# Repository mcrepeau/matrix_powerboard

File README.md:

# MatrixChain Power Board

Custom power board that feeds **four 32×32 HUB75 LED panels (4096 LEDs)** plus the **Adafruit
MatrixPortal S3** from one USB-C PD source (requested contract **20V/3A = 60W**, standard 3A cable).

Board **Rev A**: 58.35 × 50.5 mm, 2-layer 1.6 mm (1 oz default, order 2 oz if offered), all SMD on
top except the J3–J5 THT screw terminals. Orderable BOM with MPN + LCSC codes: `hardware/powerboard.csv`.

The MatrixPortal S3's MCU can drive up to 4096 LEDs, but its own USB-C port only supplies 5V/3A —
about 1500 LEDs at full white. This board lets the Portal run at full capacity: the Portal drives the
HUB75 data lines, the board supplies the panel power externally.

- **[DATASHEET.md](hardware/DATASHEET.md)** — the board's user-facing spec: electrical characteristics, connector
  pinouts, LED meanings, firmware interface, key components, assembly/bring-up.
- **[DESIGN.md](hardware/DESIGN.md)** — full design rationale, net list, per-pin hookup tables, component-selection rationale, layout and
  safety notes, open items. Source of truth for the schematic.

## Connections

```
USB-C adapter ──► PowerBoard USB-C connector (J1) ──► D1 red LED on /POW_EN (input invalid); D2/D3 green per channel
					└─ I2C connector (J2) ─► Adafruit MatrixPortal I2C connector
					└─ Screw terminals (J3) ─► Adafruit MatrixPortal power terminals (≤1A)
					└─ Screw terminals (J4) ─► HUB75 panels 1-2 (<5A)
					└─ Screw terminals (J5) ─► HUB75 panels 3-4 (<5A)
          
```

Portal links: **J3** (5V tap, ≤1A, to the M3 power screw terminals) and **J2** STEMMA QT
(GND, +3.3V, SDA, SCL). The HUB75 link to the Portal carries **data + GND only, no power** — do not
connect its 5V pins. There is no CH_EN/PG line: channels are gated purely by the supervisor
(input ≥ ≈8V ⇒ `/POW_EN` high). Panel power plugs are not reverse-protected — observe polarity.

## Behavior

| Condition | Input | D1 (red) | D2/D3 (green) | Channels | Firmware |
|---|---|---|---|---|---|
| Good PD source | ≈20V | off | on | on | read HUSB238 contract, cap power at 85% of V×I, run governor on INA226s |
| Lower contract (e.g. 15V/3A) | ≈15V | off | on | on | cap to 85% of V×I, log contract |
| Overcurrent | ≈20V | off | off (faulted ch) | limit/hiccup | INA226 alert (register) + governor |
| Dumb 5V source | ≈5V | **on** | off | off | Portal may still boot; report missing contract |
| Unplugged | 0V | off | off | off | — |

## Firmware interface

I2C on the QT bus (3.3V): HUSB238 **0x08** (source caps / negotiated contract / PDO select),
INA226 **0x40** (ch1) and **0x44** (ch2) — program CAL (0x05) at boot, alert ≈4.8A via Mask/Enable 0x06.
Boot: blank HUB75 ASAP (channels auto-enable at input ≥ ≈8V) → read contract → set power cap →
program INA226 → run (read sensors every 100ms; brightness down if a channel >4.6A for 3 reads).
Details and register maps: DATASHEET.md; rationale: DESIGN.md §5.

## Safety

Panels are **5V only**. 20V@3A and 5V@8.4A are high-energy: protection is the U9 TVS2200DRV clamp on
VBUS + HUSB238 OVP (24V) + Q1 disconnect, per-rail PTC fuses (F1 1206L100/12NR tap, F2/F3
2920L700/12MR channels), converter current limits — never rely on software for hard limits.
No input fuse (compliant PD sources only / current-limited bench supply).
Strain-relieve all cables. Full notes: DESIGN.md §9.

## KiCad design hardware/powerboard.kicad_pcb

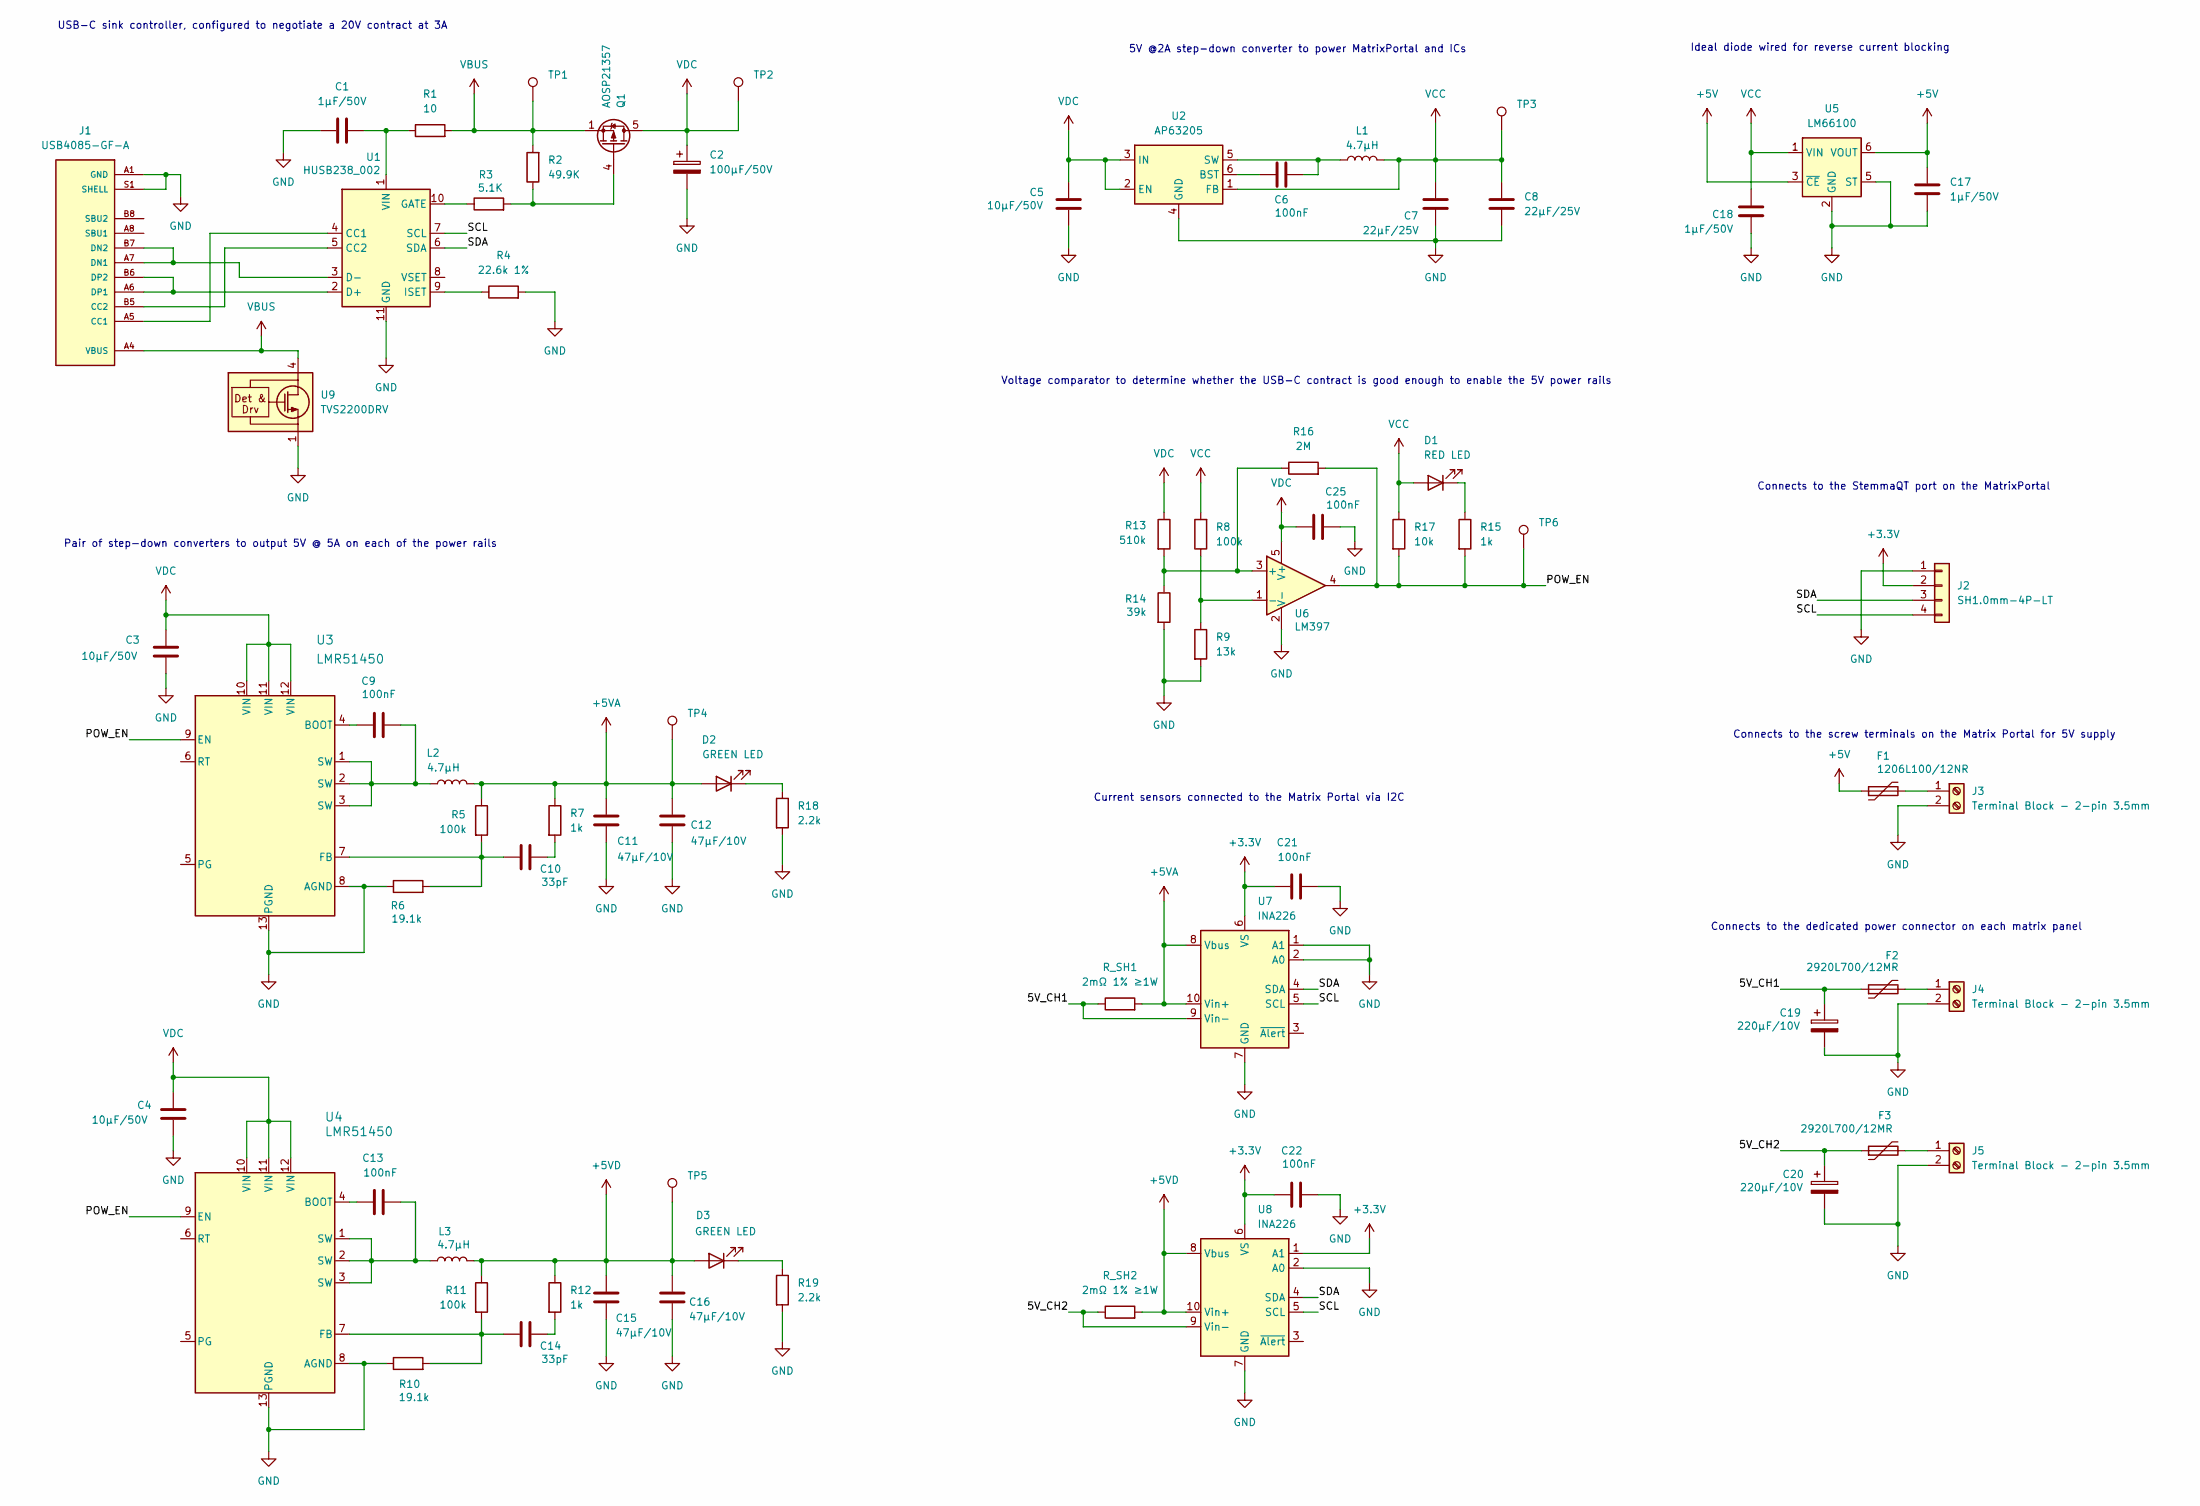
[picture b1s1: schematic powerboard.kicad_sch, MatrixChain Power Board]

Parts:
C1, C17, C18: 1µF/50V; C_0603_1608Metric; Part Number CL10A105KB8NNNC; LCSC Part # C15849
C2: 100µF/50V; CP_Elec_10x10.5; Part Number 50PEV100M10X10.5; LCSC Part # C2161609
C3, C4, C5: 10µF/50V; C_0805_2012Metric; Part Number GRM21BR61H106KE43L; LCSC Part # C440198
C6, C9, C13, C21, C22, C25: 100nF; C_0603_1608Metric; Part Number CC0603KRX7R9BB104; LCSC Part # C14663
C7, C8: 22µF/25V; C_0805_2012Metric; Part Number CL21A226MAQNNNE; LCSC Part # C45783
C10, C14: 33pF; C_0603_1608Metric; Part Number CL10C330JB8NNNC; LCSC Part # C1663
C11, C12, C15, C16: 47µF/10V; C_1206_3216Metric; Part Number CL31A476MPHNNNE; LCSC Part # C96123
C19, C20: 220µF/10V; CP_Elec_6.3x7.7; Part Number EEEFPA221XAP; LCSC Part # C278407
D1: RED LED; LED_0805_2012Metric; Part Number NCD0805R1; LCSC Part # C84256
D2, D3: GREEN LED; LED_0805_2012Metric; Part Number KT-0805G; LCSC Part # C2297
F1: 1206L100/12NR; Fuse_1206_3216Metric; Part Number 1206L100/12NR; LCSC Part # C55089856
F2, F3: 2920L700/12MR; Fuse_2920_7451Metric; Part Number 2920L700/12MR; LCSC Part # C207092
J1: USB4085-GF-A; GCT_USB4085-GF-A_REVA4; MPN USB4085-GF-A; LCSC Part # C7095263
J2: SH1.0mm-4P-LT; JST_SH_BM04B-SRSS-TB_1x04-1MP_P1.00mm_Vertical; Part Number BM04B-SRSS-TB; LCSC Part # C160390
J3, J4, J5: Terminal Block - 2-pin 3.5mm; TerminalBlock_Phoenix_PT-1,5-2-3.5-H_1x02_P3.50mm_Horizontal
L1, L2, L3: 4.7µH; L_Coilank_AAPS0650_7.7x6.6mm; Part Number APS0650M4R7A; LCSC Part # C47327217
Q1: AOSP21357; SO8SOP-8L_AOS-L; Part Number AOSP21357; LCSC Part # C541725
R1: 10; R_0603_1608Metric; Part Number 0603WAF100JT5E; LCSC Part # C22859
R2: 49.9K; R_0603_1608Metric; Part Number 0603WAF4992T5E; LCSC Part # C23184
R3: 5.1K; R_0603_1608Metric; Part Number 0603WAF5101T5E; LCSC Part # C23186
R4: 22.6k 1%; R_0603_1608Metric; Part Number CR0603FA2262G; LCSC Part # C100874
R5, R8, R11: 100k; R_0603_1608Metric; Part Number 0603WAF1003T5E; LCSC Part # C25803
R6, R10: 19.1k; R_0603_1608Metric; Part Number CR0603FA1912G; LCSC Part # C100835
R7, R12, R15: 1k; R_0603_1608Metric; Part Number 0603WAF1001T5E; LCSC Part # C21190
R9: 13k; R_0603_1608Metric; Part Number 0603WAF1302T5E; LCSC Part # C22797
R13: 510k; R_0603_1608Metric; Part Number 0603WAF5103T5E; LCSC Part # C23192
R14: 39k; R_0603_1608Metric; Part Number 0603WAF3902T5E; LCSC Part # C23153
R16: 2M; R_0603_1608Metric; Part Number 0603WAF2004T5E; LCSC Part # C22976
R17: 10k; R_0603_1608Metric; Part Number 0603WAF1002T5E; LCSC Part # C25804
R18, R19: 2.2k; R_0603_1608Metric; Part Number 0603WAF2201T5E; LCSC Part # C4190
R_SH1, R_SH2: 2mΩ 1% ≥1W; R_2512_6332Metric; Part Number RLP25FEER002; LCSC Part # C160590
TP1, TP2, TP3, TP4, TP5, TP6: TestPoint; TestPoint_Pad_D2.0mm
U1: HUSB238_002; WDFN-10-1EP_3x3mm_P0.5mm_EP1.8x2.5mm; Part Number HUSB238_002DD; LCSC Part # C7471904
U2: AP63205; TSOT-23-6; Part Number AP63205WU-7; LCSC Part # C2071056
U3, U4: LMR51450; WSON_SDRRR_TEX; Part Number LMR51450SDRRR; LCSC Part # C6890985
U5: LM66100; SOT-363_SC-70-6; Part Number LM66100DCK; LCSC Part # C2832141
U6: LM397; SOT-23-5; Part Number LM397MFX/NOPB; LCSC Part # C132076
U7, U8: INA226; TSSOP-10_3x3mm_P0.5mm; Part Number INA226AIDGSR; LCSC Part # C49851
U9: TVS2200DRV; WSON-6-1EP_2x2mm_P0.65mm_EP1x1.6mm; Part Number LMTVS2200DRVR; LCSC Part # C49330883

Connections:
+3.3V: C21.1, C22.1, J2.2, U7.6 (VS), U8.1 (A1), U8.6 (VS)
+5V: C17.1, F1.1, U5.3 (~CE), U5.6 (VOUT)
+5VA: C11.1, C12.1, D2.2 (A), L2.2, R5.1, R7.1, R_SH1.2, TP4.1 (1_1), U7.8 (Vbus), U7.10 (Vin+)
+5VD: C15.1, C16.1, D3.2 (A), L3.2, R11.1, R12.1, R_SH2.2, TP5.1 (1_1), U8.8 (Vbus), U8.10 (Vin+)
/5V_CH1: C19.1, F2.1, R_SH1.1, U7.9 (Vin-)
/5V_CH2: C20.1, F3.1, R_SH2.1, U8.9 (Vin-)
/POW_EN: R15.2, R16.2, R17.2, TP6.1 (1_1), U3.9 (EN), U4.9 (EN), U6.4
/SCL: J2.4, U1.7 (SCL), U7.5 (SCL), U8.5 (SCL)
/SDA: J2.3, U1.6 (SDA), U7.4 (SDA), U8.4 (SDA)
GND: C1.1, C2.2, C3.2, C4.2, C5.2, C7.2, C8.2, C11.2, C12.2, C15.2, C16.2, C17.2, C18.2, C19.2, C20.2, C21.2, C22.2, C25.2, J1.A1 (GND), J1.A12 (GND), J1.B1 (GND), J1.B12 (GND), J1.S1 (SHELL), J1.S2 (SHELL), J1.S3 (SHELL), J1.S4 (SHELL), J2.1, J3.2, J4.2, J5.2, R4.2, R6.1, R9.2, R10.1, R14.2, R18.2, R19.2, U1.11 (GND), U2.4 (GND), U3.8 (AGND), U3.13 (PGND), U4.8 (AGND), U4.13 (PGND), U5.2 (GND), U5.5 (ST), U6.2 (V-), U7.1 (A1), U7.2 (A0), U7.7 (GND), U8.2 (A0), U8.7 (GND), U9.1 (GND), U9.2 (GND), U9.3 (GND), U9.7 (GND)
unnamed: C9.2, L2.1, U3.1 (SW), U3.2 (SW), U3.3 (SW)
unnamed: C10.2, R7.2
unnamed: C13.2, L3.1, U4.1 (SW), U4.2 (SW), U4.3 (SW)
unnamed: C14.2, R12.2
unnamed: D1.1 (K), R15.1
unnamed: D2.1 (K), R18.1
unnamed: D3.1 (K), R19.1
unnamed: J1.A5 (CC1), U1.4 (CC1)
unnamed: J1.B5 (CC2), U1.5 (CC2)
unnamed: J1.A7 (DN1), J1.B7 (DN2), U1.3 (D-)
unnamed: J1.A6 (DP1), J1.B6 (DP2), U1.2 (D+)
unnamed: F1.2, J3.1
unnamed: F2.2, J4.1
unnamed: F3.2, J5.1
unnamed: Q1.4 (G), R2.1, R3.2
unnamed: R3.1, U1.10 (GATE)
unnamed: R4.1, U1.9 (ISET)
unnamed: C1.2, R1.1, U1.1 (VIN)
unnamed: C6.1, U2.6 (BST)
unnamed: C6.2, L1.1, U2.5 (SW)
unnamed: C9.1, U3.4 (BOOT)
unnamed: C10.1, R5.2, R6.2, U3.7 (FB)
unnamed: C13.1, U4.4 (BOOT)
unnamed: C14.1, R10.2, R11.2, U4.7 (FB)
unnamed: R13.2, R14.1, R16.1, U6.3 (+)
unnamed: R8.1, R9.1, U6.1 (-)
VBUS: J1.A4 (VBUS), J1.A9 (VBUS), J1.B4 (VBUS), J1.B9 (VBUS), Q1.1 (S), Q1.2 (S), Q1.3 (S), R1.2, R2.2, TP1.1 (1_1), U9.4 (IN), U9.5 (IN), U9.6 (IN)
VCC: C7.1, C8.1, C18.1, D1.2 (A), L1.2, R8.2, R17.1, TP3.1 (1_1), U2.1 (FB), U5.1 (VIN)
VDC: C2.1, C3.1, C4.1, C5.1, C25.1, Q1.5 (D), Q1.6 (D), Q1.7 (D), Q1.8 (D), R13.1, TP2.1 (1_1), U2.2 (EN), U2.3 (IN), U3.10 (VIN), U3.11 (VIN), U3.12 (VIN), U4.10 (VIN), U4.11 (VIN), U4.12 (VIN), U6.5 (V+)

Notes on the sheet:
Connects to the screw terminals on the Matrix Portal for 5V supply
Connects to the dedicated power connector on each matrix panel
Connects to the StemmaQT port on the MatrixPortal
Pair of step-down converters to output 5V @ 5A on each of the power rails
Voltage comparator to determine whether the USB-C contract is good enough to enable the 5V power rails
Current sensors connected to the Matrix Portal via I2C
5V @2A step-down converter to power MatrixPortal and ICs
USB-C sink controller, configured to negotiate a 20V contract at 3A
Ideal diode wired for reverse current blocking

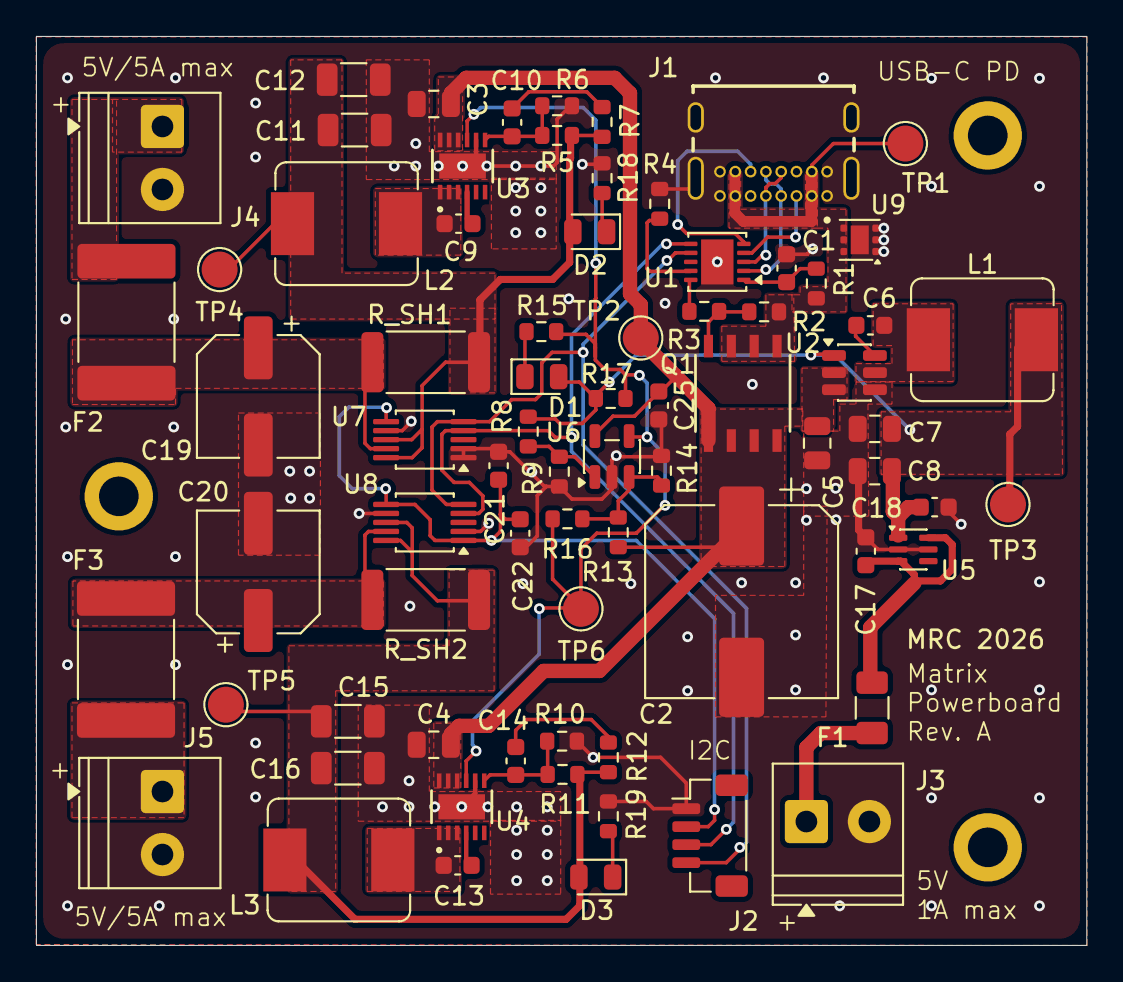
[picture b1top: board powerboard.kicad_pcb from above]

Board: 2 copper layers, 58.3 x 50.5 mm, 76 parts (0 on the bottom side), 39 nets.

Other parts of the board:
MRC 2026: MountingHole_2.2mm_M2_DIN965_Pad
Matrix PowerBoard Rev. A: MountingHole_2.2mm_M2_DIN965_Pad
